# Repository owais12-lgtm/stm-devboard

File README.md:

# STM devboard 

This is an STM32F042F6Px development board designed with GPIO pins, buttons, and USB-C, along with a buncha other features. the firmware included in the firmware folder is temp firmware and it may or may not work. 

Features

    STM32F042F6Px (32KB Flash, 6KB RAM, 48MHz)
    USB-C (USB 2.0 Full Speed via PA11/PA12)
    LP5912-3.3DRV LDO — 3.3V regulated output from 5V USB
    BOOT0 and RESET buttons
    SWD header (SWDIO, SWCLK, 3.3V, GND)
    GPIO headers — all available pins broken out

# Usage 

    Clone and open the firmware/ folder 
    Install the Rust toolchain and the thumbv6m-none-eabi target (rustup target add thumbv6m-none-eabi)

Note

This step assumes you are connected via SWD debugger. If you want to flash the firmware using USB, install rs-dfu (or similar) and skip to step 4.

    Build and flash the firmware using cargo run --release

Flashing via DFU:

    cargo build --release
    cargo objcopy --release --bin stm32-blinky -- -O binary target/thumbv6m-none-eabi/release/stm32.bin
    rdfu write --start-address 0x08000000 target/thumbv6m-none-eabi/release/stm32.bin (or similar command for an alternative dfu utility)

# render

# schematic

# PCB

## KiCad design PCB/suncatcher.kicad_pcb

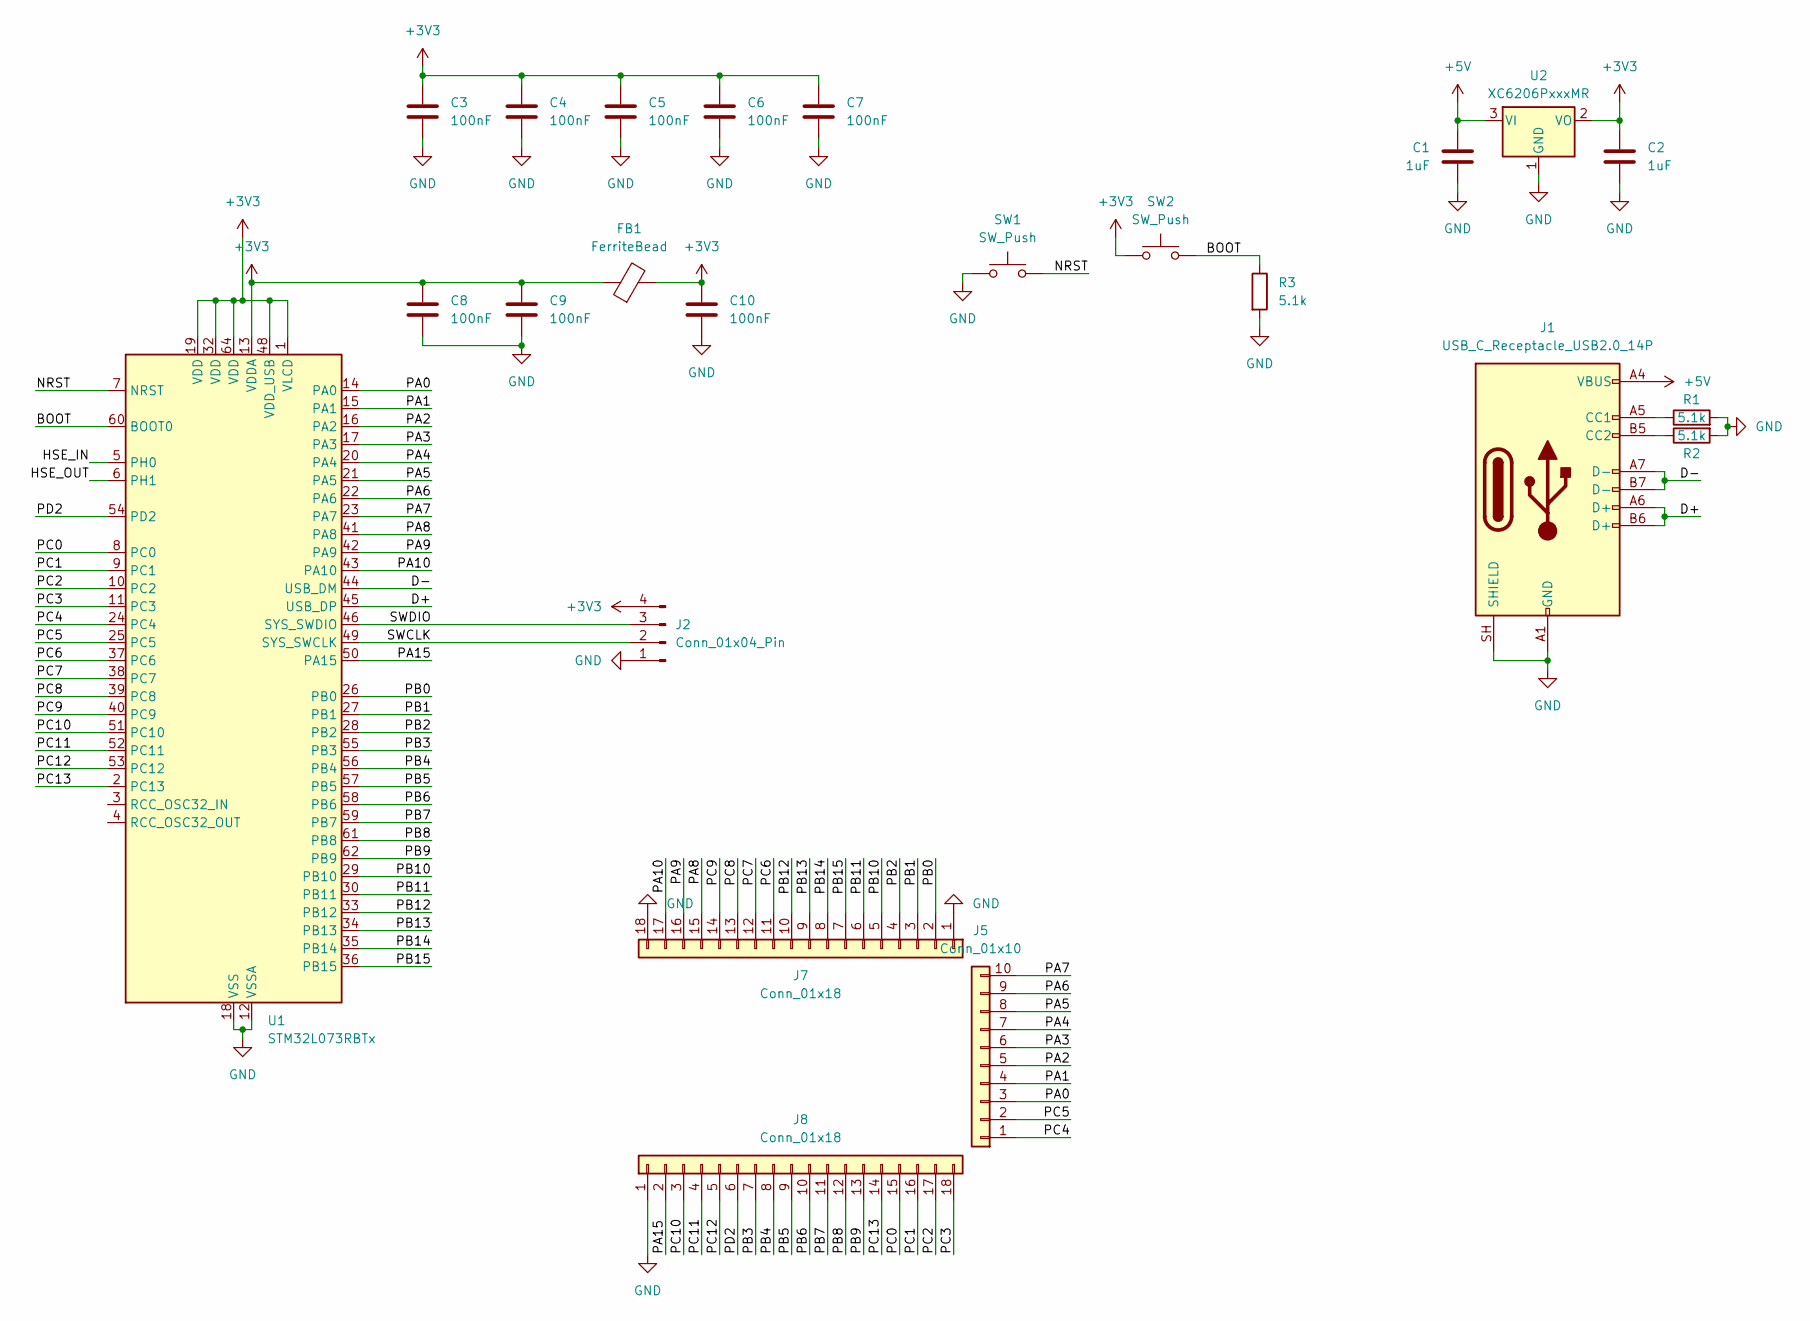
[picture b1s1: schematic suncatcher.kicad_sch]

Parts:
C1, C2: 1uF; C_0402_1005Metric_Pad0.74x0.62mm_HandSolder; LCSC Part # C52923
C3, C4, C5, C6, C7, C8, C9, C10: 100nF; C_0402_1005Metric_Pad0.74x0.62mm_HandSolder
FB1: FerriteBead; L_6.3x6.3_H3
J1: USB_C_Receptacle_USB2.0_14P; USB_C_Receptacle_GCT_USB4105-xx-A_16P_TopMnt_Horizontal; LCSC Part # C393939
J2: Conn_01x04_Pin; PinHeader_1x04_P1.00mm_Vertical
J5: Conn_01x10; PinHeader_1x10_P1.00mm_Vertical
J7, J8: Conn_01x18; PinHeader_1x18_P1.27mm_Vertical
R1, R2: 5.1k; R_0402_1005Metric_Pad0.72x0.64mm_HandSolder; LCSC Part # C25905
R3: 5.1k; R_0402_1005Metric_Pad0.72x0.64mm_HandSolder
SW1, SW2: SW_Push; SW_Tactile_SPST_NO_Straight_CK_PTS636Sx25SMTRLFS
U1: STM32L073RBTx; LQFP-64_10x10mm_P0.5mm
U2: XC6206PxxxMR; SOT-23-3; LCSC Part # C5446

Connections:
+3V3: C2.1, C3.1, C4.1, C5.1, C6.1, C7.1, C8.1, C9.1, C10.1, FB1.1, FB1.2, J2.4, SW2.1, U1.1 (VLCD), U1.13 (VDDA), U1.19 (VDD), U1.32 (VDD), U1.48 (VDD_USB), U1.64 (VDD), U2.2 (VO)
+5V: C1.1, J1.A4 (VBUS), J1.A9 (VBUS), J1.B4 (VBUS), J1.B9 (VBUS), U2.3 (VI)
/BOOT: R3.1, SW2.2, U1.60 (BOOT0)
/D+: J1.A6 (D+), J1.B6 (D+), U1.45 (USB_DP)
/D-: J1.A7 (D-), J1.B7 (D-), U1.44 (USB_DM)
/HSE_IN: U1.5 (PH0)
/HSE_OUT: U1.6 (PH1)
/NRST: SW1.2, U1.7 (NRST)
/PA0: J5.3, U1.14 (PA0)
/PA1: J5.4, U1.15 (PA1)
/PA2: J5.5, U1.16 (PA2)
/PA3: J5.6, U1.17 (PA3)
/PA4: J5.7, U1.20 (PA4)
/PA5: J5.8, U1.21 (PA5)
/PA6: J5.9, U1.22 (PA6)
/PA7: J5.10, U1.23 (PA7)
/PA8: J7.15, U1.41 (PA8)
/PA9: J7.16, U1.42 (PA9)
/PA10: J7.17, U1.43 (PA10)
/PA15: J8.2, U1.50 (PA15)
/PB0: J7.2, U1.26 (PB0)
/PB1: J7.3, U1.27 (PB1)
/PB2: J7.4, U1.28 (PB2)
/PB3: J8.7, U1.55 (PB3)
/PB4: J8.8, U1.56 (PB4)
/PB5: J8.9, U1.57 (PB5)
/PB6: J8.10, U1.58 (PB6)
/PB7: J8.11, U1.59 (PB7)
/PB8: J8.12, U1.61 (PB8)
/PB9: J8.13, U1.62 (PB9)
/PB10: J7.5, U1.29 (PB10)
/PB11: J7.6, U1.30 (PB11)
/PB12: J7.10, U1.33 (PB12)
/PB13: J7.9, U1.34 (PB13)
/PB14: J7.8, U1.35 (PB14)
/PB15: J7.7, U1.36 (PB15)
/PC0: J8.15, U1.8 (PC0)
/PC1: J8.16, U1.9 (PC1)
/PC2: J8.17, U1.10 (PC2)
/PC3: J8.18, U1.11 (PC3)
/PC4: J5.1, U1.24 (PC4)
/PC5: J5.2, U1.25 (PC5)
/PC6: J7.11, U1.37 (PC6)
/PC7: J7.12, U1.38 (PC7)
/PC8: J7.13, U1.39 (PC8)
/PC9: J7.14, U1.40 (PC9)
/PC10: J8.3, U1.51 (PC10)
/PC11: J8.4, U1.52 (PC11)
/PC12: J8.5, U1.53 (PC12)
/PC13: J8.14, U1.2 (PC13)
/PD2: J8.6, U1.54 (PD2)
/SWCLK: J2.2, U1.49 (SYS_SWCLK)
/SWDIO: J2.3, U1.46 (SYS_SWDIO)
GND: C1.2, C2.2, C3.2, C4.2, C5.2, C6.2, C7.2, C8.2, C9.2, C10.2, J1.A1 (GND), J1.A12 (GND), J1.B1 (GND), J1.B12 (GND), J1.SH (SHIELD), J2.1, J7.1, J7.18, J8.1, R1.2, R2.2, R3.2, SW1.1, U1.12 (VSSA), U1.18 (VSS), U1.31 (VSS), U1.47 (VSS), U1.63 (VSS), U2.1 (GND)
unnamed: J1.A5 (CC1), R1.1
unnamed: J1.B5 (CC2), R2.1

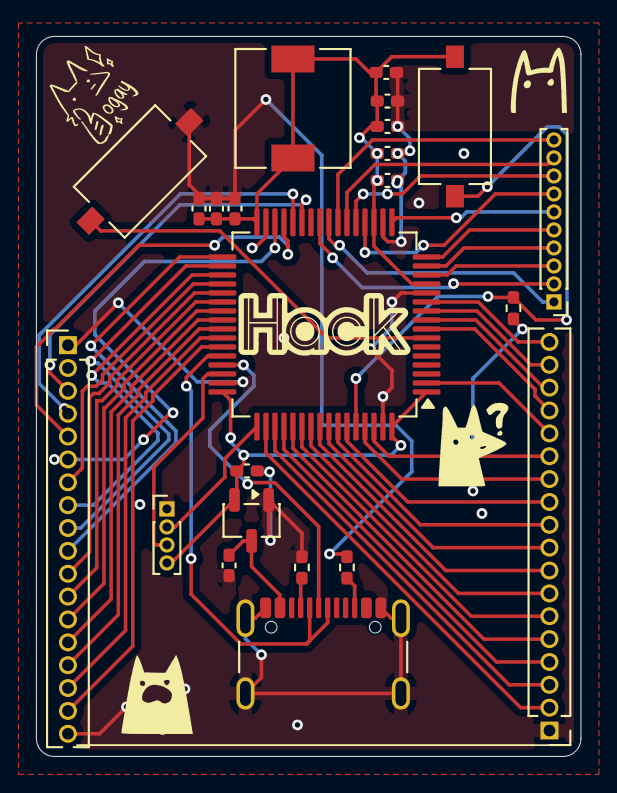
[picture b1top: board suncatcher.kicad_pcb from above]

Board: 2 copper layers, 30.2 x 40.0 mm, 23 parts (0 on the bottom side), 54 nets.
